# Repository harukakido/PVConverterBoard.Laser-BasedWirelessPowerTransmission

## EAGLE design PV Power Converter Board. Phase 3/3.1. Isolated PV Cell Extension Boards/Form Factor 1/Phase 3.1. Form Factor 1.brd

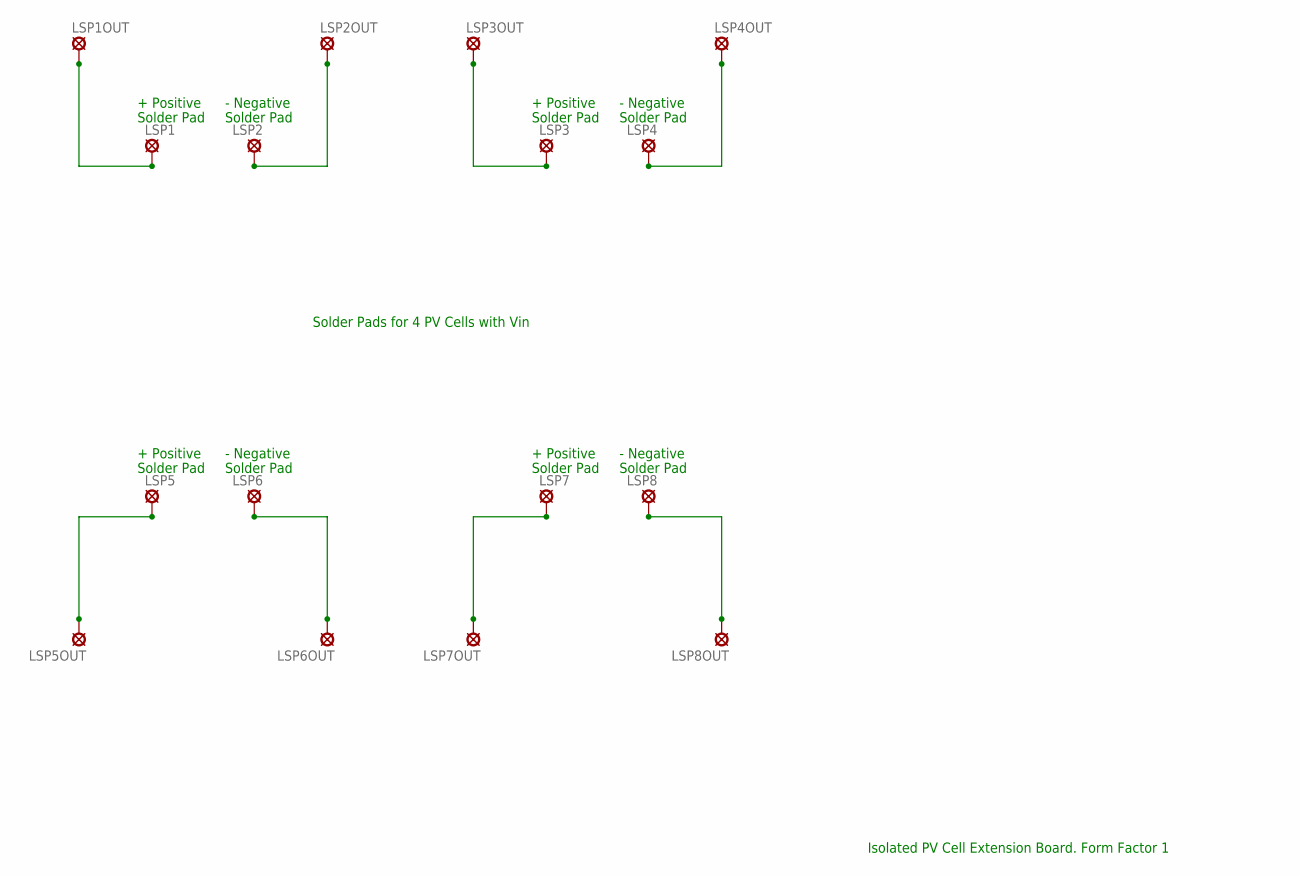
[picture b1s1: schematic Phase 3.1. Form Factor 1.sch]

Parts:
LSP1, LSP1OUT, LSP2, LSP2OUT, LSP3, LSP3OUT, LSP4, LSP4OUT, LSP5, LSP5OUT, LSP6, LSP6OUT, LSP7, LSP7OUT, LSP8, LSP8OUT: LSP10

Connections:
unnamed: LSP1.MP, LSP1OUT.MP
unnamed: LSP2.MP, LSP2OUT.MP
unnamed: LSP3.MP, LSP3OUT.MP
unnamed: LSP4.MP, LSP4OUT.MP
unnamed: LSP5.MP, LSP5OUT.MP
unnamed: LSP6.MP, LSP6OUT.MP
unnamed: LSP7.MP, LSP7OUT.MP
unnamed: LSP8.MP, LSP8OUT.MP

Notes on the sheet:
Solder Pad
+ Positive
- Negative
Solder Pads for 4 PV Cells with Vin
Isolated PV Cell Extension Board. Form Factor 1

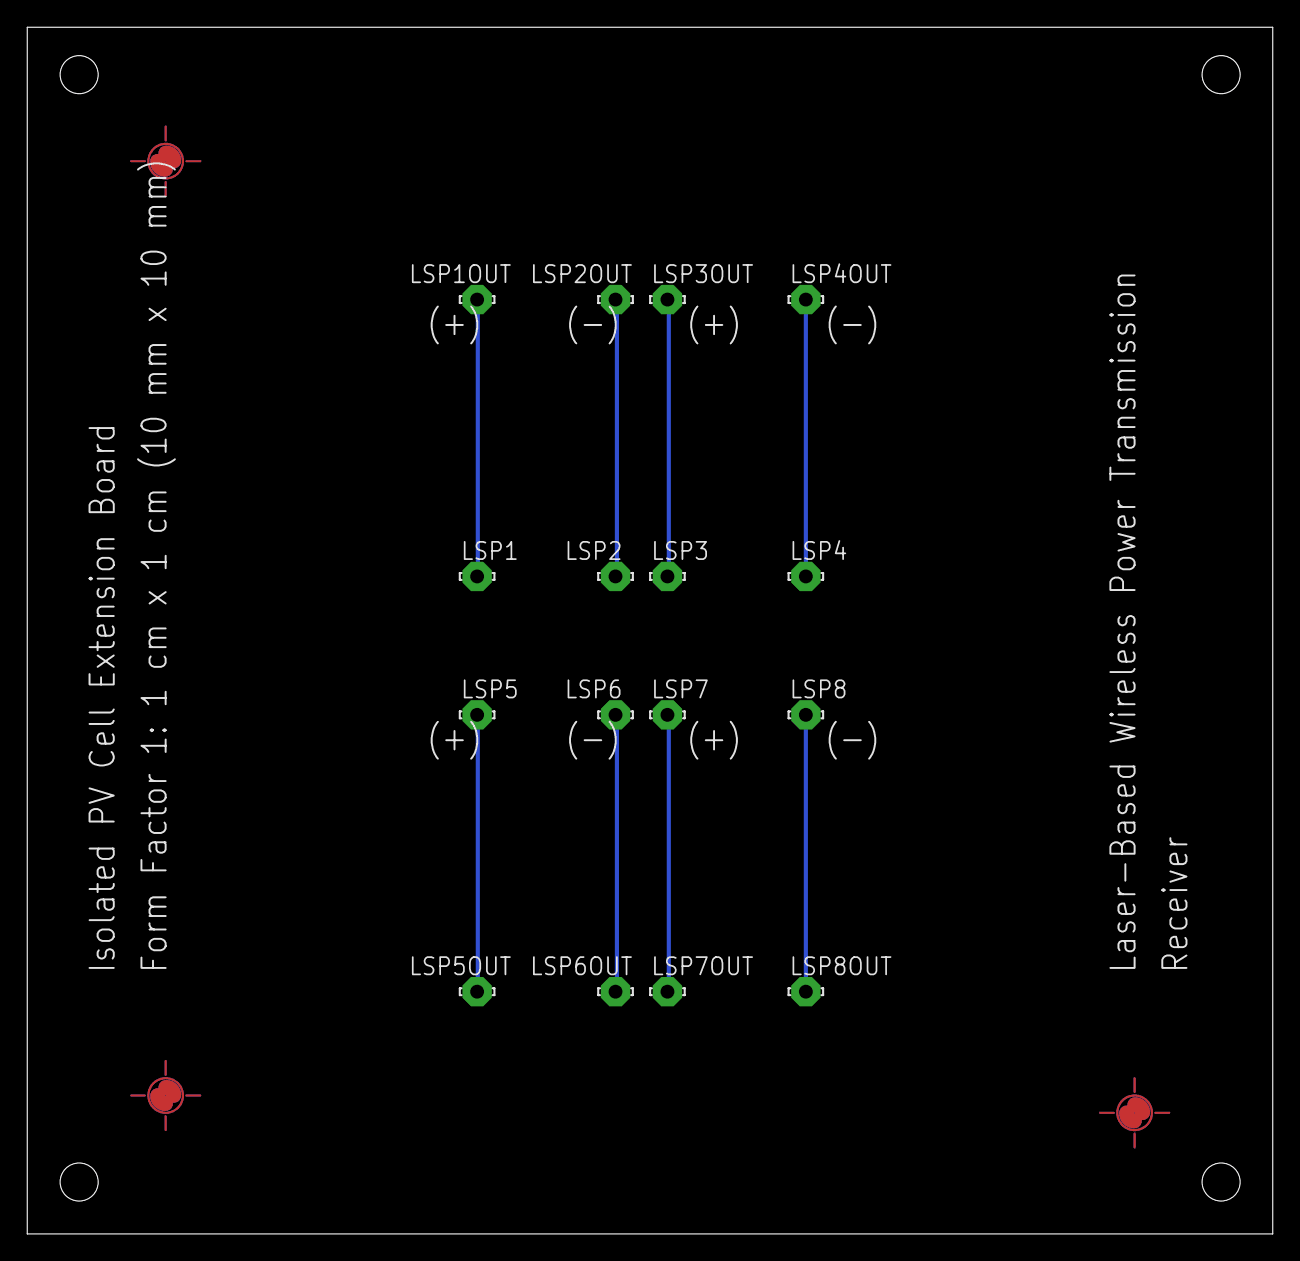
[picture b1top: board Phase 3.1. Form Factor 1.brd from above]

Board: 2 copper layers, 91.4 x 88.6 mm, 23 parts (0 on the bottom side), 8 nets.

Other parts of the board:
STAND1, STAND2, STAND3, STAND4: MOUNTHOLE_110MIL
U$1, U$2, U$3: PASS-ROUND

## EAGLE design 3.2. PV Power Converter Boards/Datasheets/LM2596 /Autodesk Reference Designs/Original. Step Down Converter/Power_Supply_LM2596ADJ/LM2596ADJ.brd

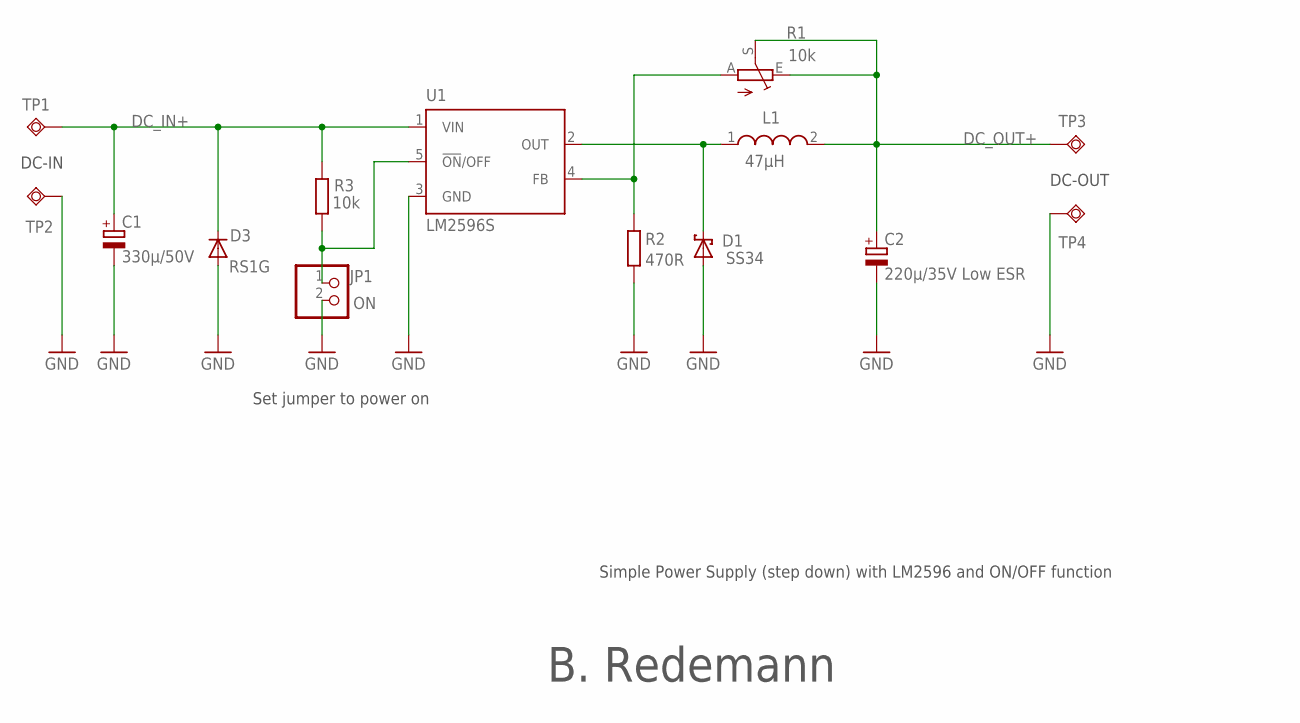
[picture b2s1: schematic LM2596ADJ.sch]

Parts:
C1: 330µ/50V; PANASONIC_G
C2: 220µ/35V Low ESR; PANASONIC_F
D1: SS34; SMB
D3: RS1G; DO214AC
JP1: ON; 1X02
L1: 47µH; WE-PD_1260/1245/1280/1210
R1: 10k; RJ9W
R2: 470R; M0805
R3: 10k; M0805
TP1: DC_IN; P1-13Y
TP2, TP4: GND; P1-13Y
TP3: DC_OUT; P1-13Y
U1: LM2596S; TO263-5

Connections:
DC_IN+: C1.+, D3.C, R3.2, TP1.TP, U1.1 (VIN)
DC_OUT+: C2.+, L1.2, R1.E, R1.S, TP3.TP
GND: C1.-, C2.-, D1.A, D3.A, JP1.2, R2.1, TP2.TP, TP4.TP, U1.3 (GND)
unnamed: D1.C, L1.1, U1.2 (OUT)
unnamed: R1.A, R2.2, U1.4 (FB)
unnamed: JP1.1, R3.1, U1.5 (!ON!/OFF)

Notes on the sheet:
B. Redemann
Simple Power Supply (step down) with LM2596 and ON/OFF function
DC-IN
DC-OUT
Set jumper to power on

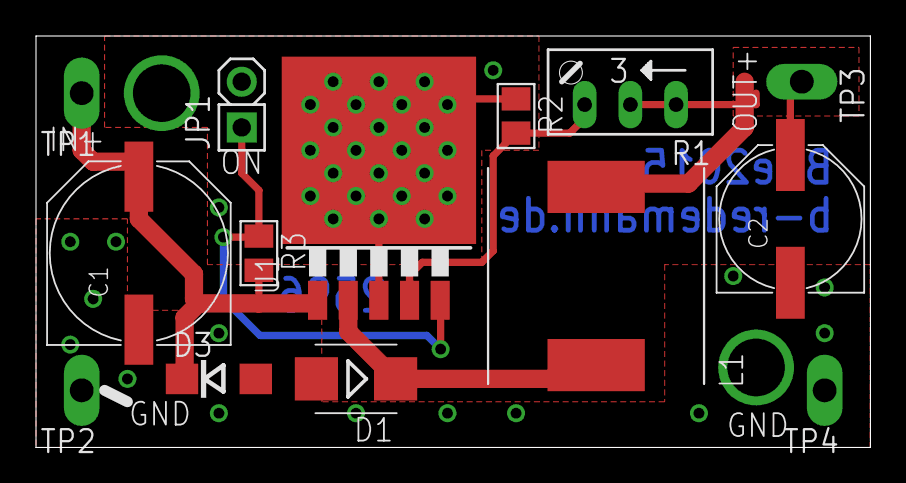
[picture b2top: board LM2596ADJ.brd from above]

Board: 2 copper layers, 46.4 x 22.9 mm, 14 parts (0 on the bottom side), 6 nets.

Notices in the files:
parts and their libraries:
Wurth_Elektronik_Passive_rev15b: Copyright: Würth Elektronik
